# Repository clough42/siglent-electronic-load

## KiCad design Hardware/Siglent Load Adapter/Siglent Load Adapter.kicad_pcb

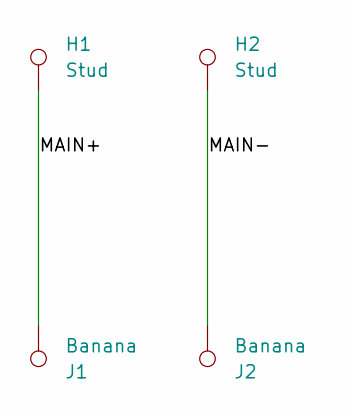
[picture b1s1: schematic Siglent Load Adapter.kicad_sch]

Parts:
H1, H2: Stud; M6_Binding_Stud
J1, J2: Banana; Pomona_73096_4mm_Safety_jack

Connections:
/MAIN+: H1.1, J1.1
/MAIN-: H2.1, J2.1

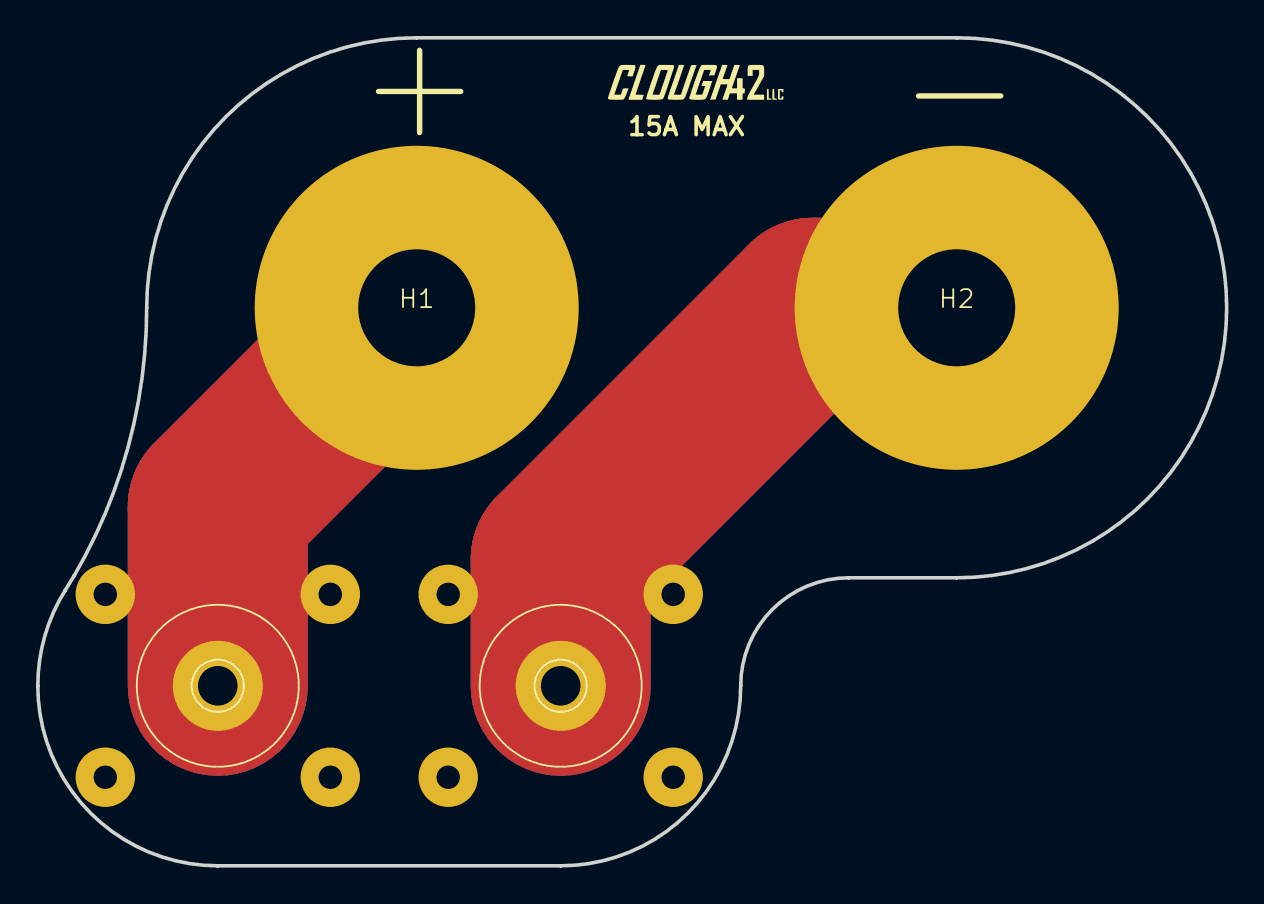
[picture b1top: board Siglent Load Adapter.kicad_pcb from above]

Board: 2 copper layers, 66.0 x 46.0 mm, 4 parts (0 on the bottom side), 2 nets.

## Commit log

2023-07-20 Initial design.
2023-07-20 3D model
2023-07-20 Changed board thickness to 2mm

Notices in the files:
Hardware/Siglent Load Adapter/Siglent Load Adapter.kicad_pcb:
Copyright (C) 2023
